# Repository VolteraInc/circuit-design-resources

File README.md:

# circuit-design-resources
Gerbers and other useful things for circuit designers.

For EAGLE users, use voltera_EAGLE_community_lib.lbr to access the part files for the templates and substrates.

For other CAD tools, dimensioned drawings and raw gerbers are available.

Feel like contributing to the Voltera community? We'd appreciate your help in creating template parts libraries for other CAD tools. If you create a library, let us know and we'll link to your work!

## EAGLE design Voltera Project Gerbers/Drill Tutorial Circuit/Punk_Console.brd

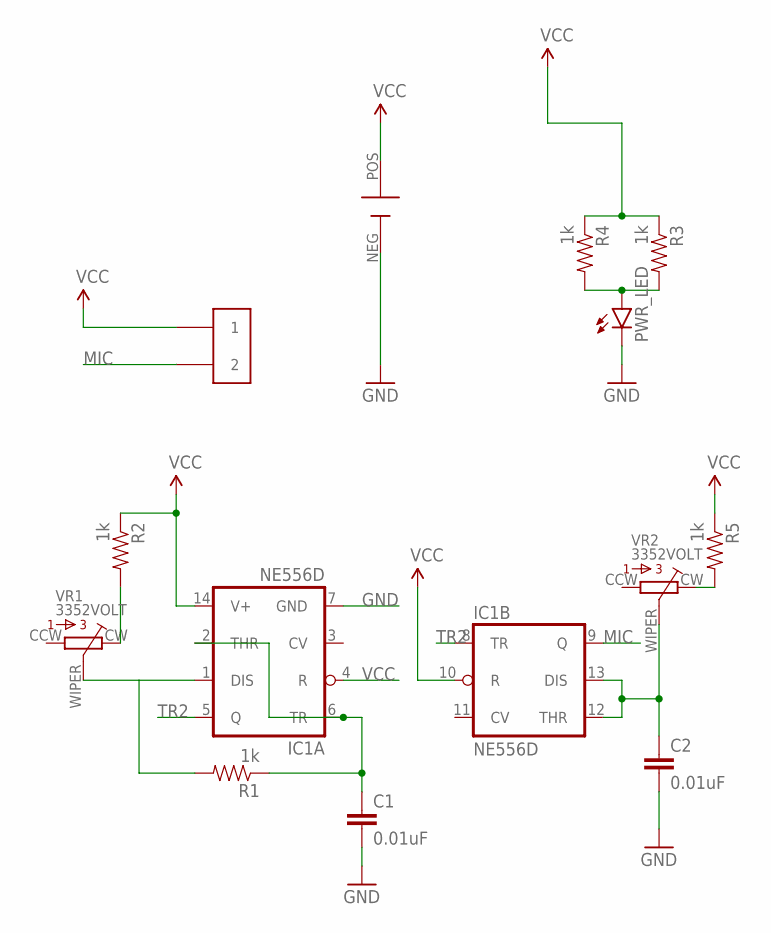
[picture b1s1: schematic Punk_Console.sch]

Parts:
C1, C2: 0.01uF; 1206
IC1: NE556D; SO14
PWR_LED: LED1206; LED-1206
R1, R2, R3, R4, R5: 1k; 1206
U$4: SMD_BATTERY_9VVIA; VIA_BATTERY_PADS
U$5: BUZZER; BUZZER_PS1240P02BT
VR1, VR2: 3352VOLT; 3352E_VOLT_VIA

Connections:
GND: C1.2, C2.2, IC1.7 (GND), PWR_LED.C, U$4.NEG
MIC: IC1.9 (Q), U$5.P$2 (2)
unnamed: PWR_LED.A, R3.2, R4.2
unnamed: IC1.1 (DIS), R1.2, VR1.WIPER (2)
unnamed: R2.2, VR1.CW (3)
unnamed: R5.2, VR2.CW (3)
THR1: C1.1, IC1.2 (THR), IC1.6 (TR), R1.1
THR2: C2.1, IC1.12 (THR), IC1.13 (DIS), VR2.WIPER (2)
TR2: IC1.5 (Q), IC1.8 (TR)
VCC: IC1.4 (R), IC1.10 (R), IC1.14 (V+), R2.1, R3.1, R4.1, R5.1, U$4.POS, U$5.P$1 (1)

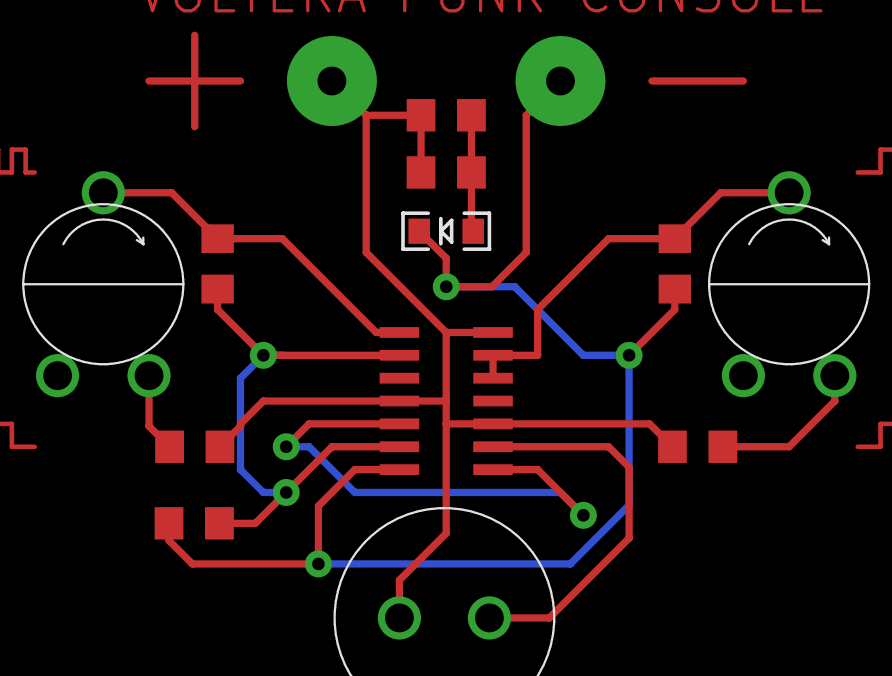
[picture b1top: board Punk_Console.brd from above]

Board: 2 copper layers, 13 parts (0 on the bottom side), 10 nets.

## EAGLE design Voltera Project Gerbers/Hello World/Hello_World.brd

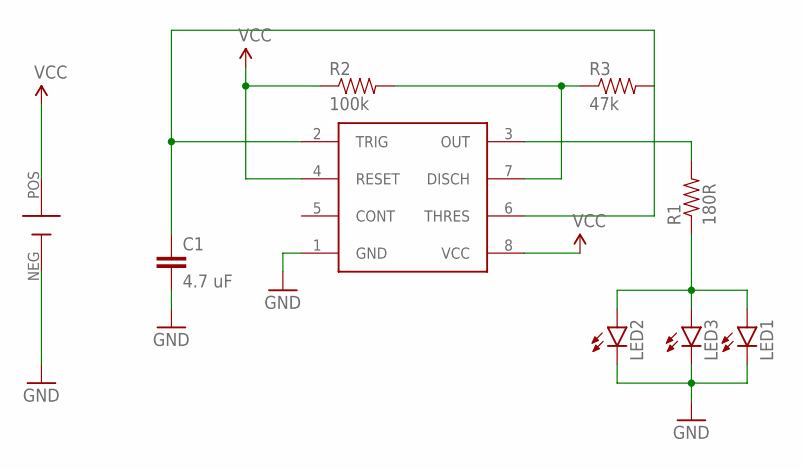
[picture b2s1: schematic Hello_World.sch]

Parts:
C1: 4.7 uF; C1206
LED1, LED2, LED3: LED1206; LED-1206
R1: 180R; 1206
R2: 100k; 1206
R3: 47k; 1206
U1: NE555PSR; PS_R-PDSO-G8
U$1: SMD_BATTERY_9V; SMD_BATTERY_PADS

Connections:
GND: C1.2, LED1.C, LED2.C, LED3.C, U1.1 (GND), U$1.NEG
unnamed: LED1.A, LED2.A, LED3.A, R1.1
unnamed: R2.2, R3.1, U1.7 (DISCH)
unnamed: R1.2, U1.3 (OUT)
unnamed: C1.1, R3.2, U1.2 (TRIG), U1.6 (THRES)
VCC: R2.1, U1.4 (RESET), U1.8 (VCC), U$1.POS

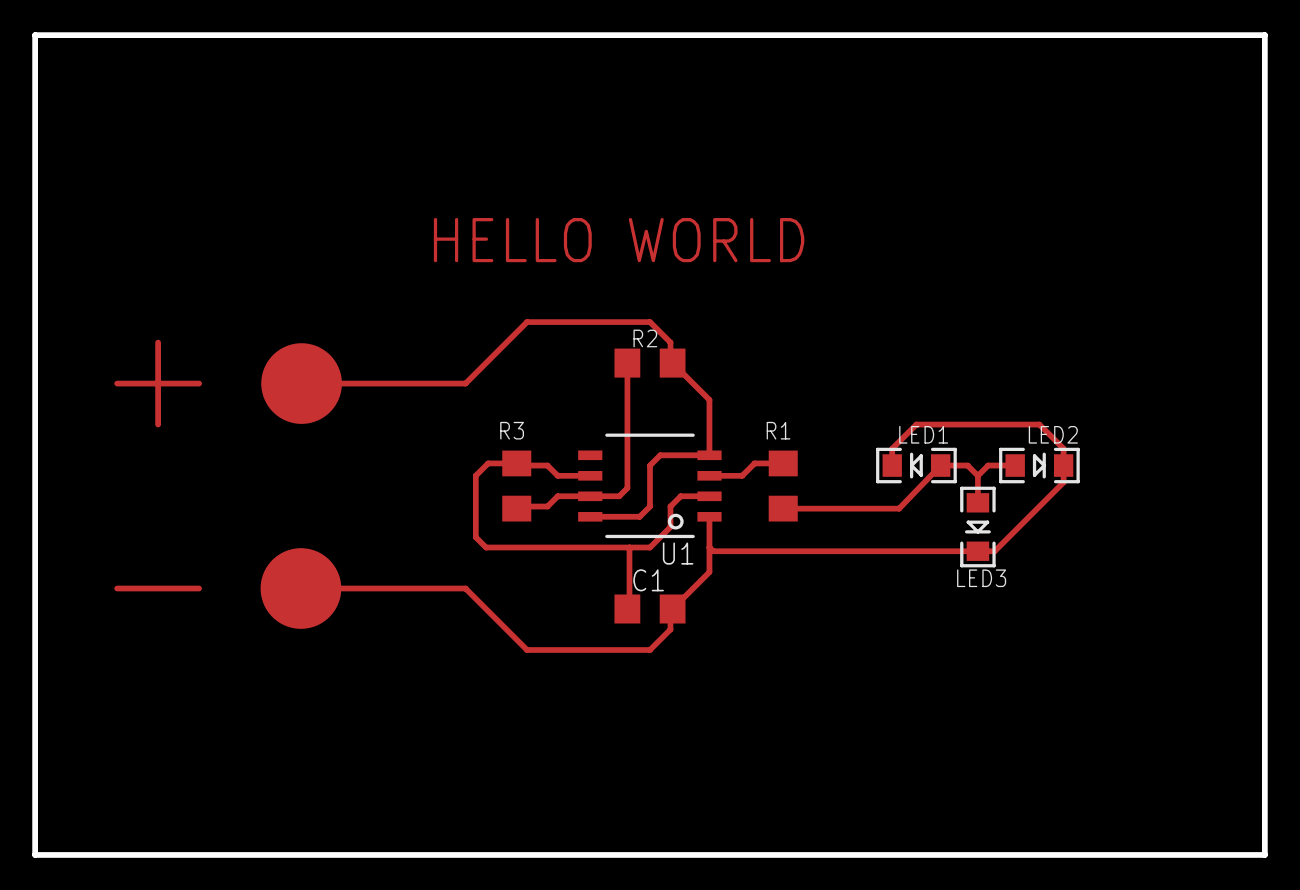
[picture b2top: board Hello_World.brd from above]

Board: 2 copper layers, 76.2 x 50.8 mm, 9 parts (0 on the bottom side), 6 nets.

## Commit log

2017-03-23 Added Voltera template and substrate resources
2017-03-23 updated README.txt
2017-03-23 Added EAGLE community lib
2017-04-03 Added Dimensioned USB Template
2017-05-19 Elinated duplicate gerber files
2017-06-30 Added Double Sided hello world
2017-09-07 Generated design blocks. Updated Photon schematic
2017-09-08 Updated Drill Hello World for rivets
2017-09-14 Removed contour arduino, updated design blocks and compressed files
2017-11-30 Created 2x3 and 3x4 FR1 templates. Added 'fab' version of the templates
2018-02-07 Added drill tutorial (Punk console) circuit and gerbers
2018-02-14 Updated Punk Console circuit
2018-03-14 Updated 2x3, 3x4, 4x5 drill files
2018-03-14 Added hello world tutorial
2018-04-03 Updated 2x3, 3x4, 4x5 - converted vias to proper fiducials
2018-04-18 Added FR1 Arduino Uno template (correctly sized holes for 1.6mm drill vias)
2018-04-18 Added zip folder for lib
2018-04-18 Added Voltera DRU file to repo
2018-04-18 Zipped DRU
2018-08-24 Created FAB version for evertying, removed bad versions
2018-12-04 Added Feather board, updated community library and added substrate gerbers
2018-12-11 Added feather, cleaned up community library. Added v2 for 2x3, 3x4 and 4x5 boards. Simplified the library and reorganized tree directory
2018-12-11 Zipped the CAM, DRU and library
2019-02-26 Cleaned up template gerbers. Fixed punk console sch. (could not open with eagle 9)
2019-02-26 Updated punk console .zip
2019-03-07 Corrected 2x3 FR board size
2019-03-20 Removed 'raw' templates to avoid confusion. Added trestrict, vrestrict and brestrict to feather board
2019-04-05 Made updates to the feather template
2019-06-05 Updated 4x5 to make fiducial a bit smaller to meet our bounds. Added 'fr4' silkscreen to 2x3, 3x4 and 4x5 substrates
2020-07-24 Added RAW USB Template that we manufacture

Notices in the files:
parts and their libraries:
SparkFun-LED: Licensing: Creative Commons ShareAlike 4.0 International - https://creativecommons.org/licenses/by-sa/4.0
SparkFun-LED: Licensing: CC v3.0 Share-Alike You are welcome to use this library for commercial purposes.
